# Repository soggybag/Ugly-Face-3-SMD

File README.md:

# Ugly Face 3 (SMD)

*Silkscreen name: Deformis v2.*

A gated, envelope-controlled square-wave synth fuzz for guitar, in a Hammond 1590B. A TL072 preamp (gain 201) gates and bends a TLC555 oscillator, with a **MIX** control to blend the dry fuzz with the synth tone. SMD parts are assembled by JLCPCB; the pots, LED, vactrol and wiring are hand-soldered.

## How it works

The guitar is amplified ×201 by U1A into a clipped square, which then does three things:

1. **Gate.** It's AC-coupled onto the 555's RESET pin. THRESHOLD sets the bias around the 555's ~1.0 V reset point, so the oscillator switches on and off every guitar cycle and restarts in step with the note (hard sync).
2. **Pitch bend.** It lights a DIY vactrol (LED + LDR). The LDR sits across the 555's timing resistance, so playing harder raises the pitch.
3. **Dry path.** It feeds the MIX control. U1B sums the dry fuzz and the 555 square (×4.1) → VOLUME → OUT.

Schematic: [UglyFace_03_schematic.pdf](UglyFace_03_schematic.pdf) · Layout: [UglyFace_03_layout.pdf](UglyFace_03_layout.pdf)

## Controls

| Knob | Part | Function |
|---|---|---|
| ENVELOPE | RV1 A10k (v1.3; v1.1 B1k) | How much the playing level drives the vactrol (pitch bend); fully CCW = off |
| THRESHOLD | SW1 toggle (v1.1) | GATED / GLITCH / ON. GLITCH sits on the 555's reset threshold, set once with the RV2 trimmer |
| FREQUENCY | RV3 C100k | Oscillator pitch (measured ~33 Hz to ~5 kHz) |
| MIX | RV4 B10k | Clean guitar (v1.1) ↔ synth square |
| VOLUME | RV5 A100k | Output level |

## Build notes

- **Hand-soldered:** four Alpha 16 mm pots, the THRESHOLD toggle (Taiway 100 ON-OFF-ON), the RV2 3362P 10k trimmer, the 3 mm LED (D2), the DIY vactrol U3 (LED + LDR in heat-shrink or a light-tight box), and the wire pads (9V/GND, IN/IG, OUT/OG, LED−/LG).
- **v1.0 boards only, recommended mod:** tack a **100 µF electrolytic across C4** (+ to VB, the MIX pot's middle-pin side). The stock 22 µF ceramic loses capacitance at 4.4 V. Without the mod, oscillator ripple on VB feeds back through the gain-201 preamp into the gate, and THRESHOLD becomes very sticky (on at 75%, off at 25%).
- Power: 9 V centre-negative; SS14 series reverse-polarity protection; ~4.3 mA (+ ~3.5 mA LED).

## Status

- **v1.1 (2026-10-03, JLC files generated):** C4 100 µF, 22k into RESET, RC-filtered 555 supply, C7 2.2 µ, C12/C13 1 µ, clean dry path (U4A) for MIX, buffered VB (U4B), THRESHOLD toggle + GLITCH trimmer. Details in [docs/Build Notes.md](docs/Build%20Notes.md).
- **v1.3 (2026-10-19, JLC files generated, not ordered):** new envelope (U5 LM358 detector from the clean DRY_OUT, Q1 current sink for the vactrol LED, DECAY trimmer RV6), ENVELOPE pot A10k, BAT54S RESET clamp, R21 15k, R13 220k, slotted Taiway footprint. Details: [docs/v1.3 Envelope.md](docs/v1.3%20Envelope.md).

- Boards received from JLCPCB 2026-10-01; bench tested 2026-10-02; **working with a guitar.** Measurements: [docs/Test Procedure.md](docs/Test%20Procedure.md).
- **Known issues (v1.0) / next revision** ([docs/Build Notes.md](docs/Build%20Notes.md)):
  - C4 → 100 µF.
  - FREQUENCY low end too low (33 Hz); C10 470n ceramic behaves like ~235n under bias, so use a film/C0G cap and retune.
  - Envelope weak (LDR choice / LED drive).
  - C12/C13 coupling caps cut below ~100 Hz.
  - Series resistor on the 555 RESET pin (CMOS protection; the pin is driven below ground every cycle).
  - THRESHOLD could become a 3-position switch.
- Ideas for the family: [Ugly Face Roadmap.md](Ugly%20Face%20Roadmap.md).

## Repository layout

```
UglyFace_03.kicad_pro / .kicad_sch / .kicad_pcb / .kicad_dru   KiCad 10 project
UglyFace.pretty/, fp-lib-table                              project footprints
3dmodels/        pot and enclosure models (${KIPRJMOD})
docs/            test procedure (with measurements) and build notes
enclosure/       panel art (Affinity + PDF/SVG exports)
*.pdf, *.png     schematic, layout and renders
```

Opens with KiCad 10. Libraries and 3D models are project-local or from KiCad's standard library.

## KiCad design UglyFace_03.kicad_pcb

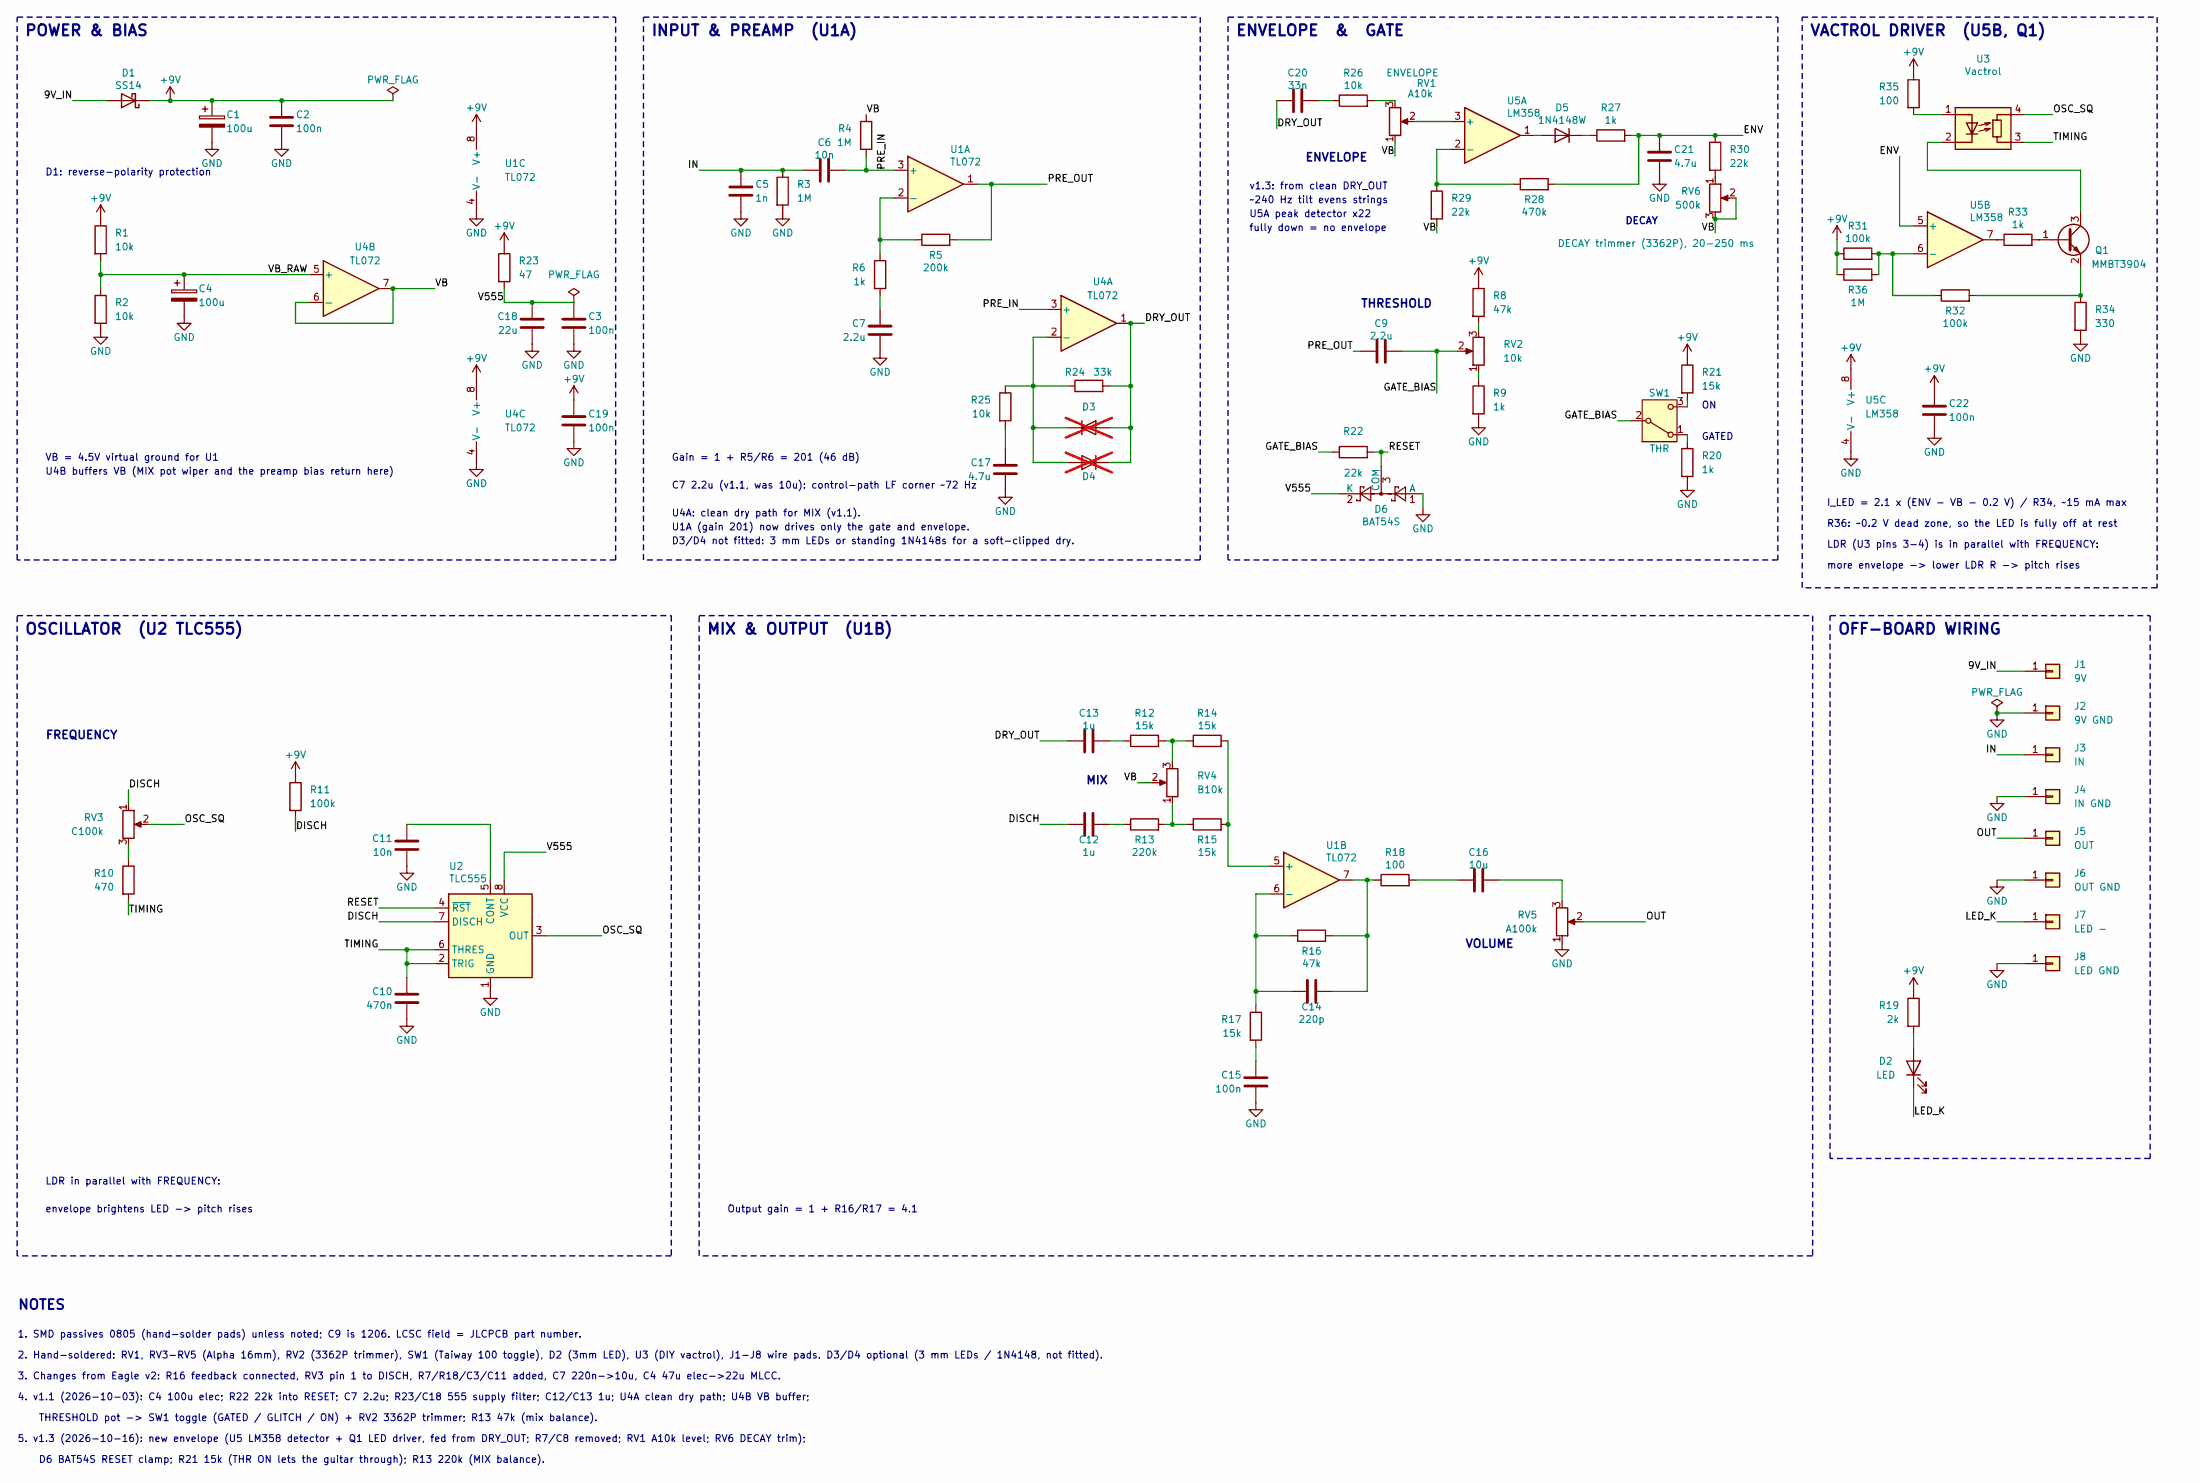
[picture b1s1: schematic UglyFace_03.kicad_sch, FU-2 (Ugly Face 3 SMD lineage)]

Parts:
C1, C4: 100u; CP_Elec_6.3x7.7; LCSC C970685
C2, C3, C15, C19, C22: 100n; C_0805_2012Metric_Pad1.18x1.45mm_HandSolder; LCSC C49678
C5: 1n; C_0805_2012Metric_Pad1.18x1.45mm_HandSolder; LCSC C46653
C6, C11: 10n; C_0805_2012Metric_Pad1.18x1.45mm_HandSolder; LCSC C1710
C7: 2.2u; C_0805_2012Metric_Pad1.18x1.45mm_HandSolder; LCSC C377773
C9: 2.2u; C_1206_3216Metric_Pad1.33x1.80mm_HandSolder; LCSC C50254
C10: 470n; C_0805_2012Metric_Pad1.18x1.45mm_HandSolder; LCSC C13967
C12, C13: 1u; C_0805_2012Metric_Pad1.18x1.45mm_HandSolder; LCSC C28323
C14: 220p; C_0805_2012Metric_Pad1.18x1.45mm_HandSolder; LCSC C107145
C16: 10u; C_0805_2012Metric_Pad1.18x1.45mm_HandSolder; LCSC C15850
C17, C21: 4.7u; C_0805_2012Metric_Pad1.18x1.45mm_HandSolder; LCSC C1779
C18: 22u; C_1206_3216Metric_Pad1.33x1.80mm_HandSolder; LCSC C12891
C20: 33n; C_0805_2012Metric_Pad1.18x1.45mm_HandSolder; LCSC C1739
D1: SS14; D_SMA_Handsoldering; LCSC C2480
D2: LED; LED_D3.0mm
D3, D4: 1N4148/LED; D_THT_Standing_3mm_P2.54_Compact; not fitted
D5: 1N4148W; D_SOD-123; LCSC C81598
D6: BAT54S; SOT-23; LCSC C19726
J1: 9V; SolderWire-0.5sqmm_1x01_D0.9mm_OD2.1mm
J2: 9V GND; SolderWire-0.5sqmm_1x01_D0.9mm_OD2.1mm
J3: IN; SolderWire-0.5sqmm_1x01_D0.9mm_OD2.1mm
J4: IN GND; SolderWire-0.5sqmm_1x01_D0.9mm_OD2.1mm
J5: OUT; SolderWire-0.5sqmm_1x01_D0.9mm_OD2.1mm
J6: OUT GND; SolderWire-0.5sqmm_1x01_D0.9mm_OD2.1mm
J7: LED -; SolderWire-0.5sqmm_1x01_D0.9mm_OD2.1mm
J8: LED GND; SolderWire-0.5sqmm_1x01_D0.9mm_OD2.1mm
Q1: MMBT3904; SOT-23; LCSC C20526
R1, R2, R25, R26: 10k; R_0805_2012Metric_Pad1.20x1.40mm_HandSolder; LCSC C17414
R3, R4, R36: 1M; R_0805_2012Metric_Pad1.20x1.40mm_HandSolder; LCSC C17514
R5: 200k; R_0805_2012Metric_Pad1.20x1.40mm_HandSolder; LCSC C17539
R6, R9, R20, R27, R33: 1k; R_0805_2012Metric_Pad1.20x1.40mm_HandSolder; LCSC C17513
R8, R16: 47k; R_0805_2012Metric_Pad1.20x1.40mm_HandSolder; LCSC C17713
R10: 470; R_0805_2012Metric_Pad1.20x1.40mm_HandSolder; LCSC C17710
R11, R31, R32: 100k; R_0805_2012Metric_Pad1.20x1.40mm_HandSolder; LCSC C149504
R12, R14, R15, R17, R21: 15k; R_0805_2012Metric_Pad1.20x1.40mm_HandSolder; LCSC C17475
R13: 220k; R_0805_2012Metric_Pad1.20x1.40mm_HandSolder; LCSC C17556
R18, R35: 100; R_0805_2012Metric_Pad1.20x1.40mm_HandSolder; LCSC C17408
R19: 2k; R_0805_2012Metric_Pad1.20x1.40mm_HandSolder; LCSC C17604
R22, R29, R30: 22k; R_0805_2012Metric_Pad1.20x1.40mm_HandSolder; LCSC C17560
R23: 47; R_0805_2012Metric_Pad1.20x1.40mm_HandSolder; LCSC C17714
R24: 33k; R_0805_2012Metric_Pad1.20x1.40mm_HandSolder; LCSC C17633
R28: 470k; R_0805_2012Metric_Pad1.20x1.40mm_HandSolder; LCSC C17709
R34: 330; R_0805_2012Metric_Pad1.20x1.40mm_HandSolder; LCSC C17630
RV1: A10k; Potentiometer_Alpha_16mm_Vertical
RV2: 10k; Potentiometer_Bourns_3362P_Vertical
RV3: C100k; Potentiometer_Alpha_16mm_Vertical
RV4: B10k; Potentiometer_Alpha_16mm_Vertical
RV5: A100k; Potentiometer_Alpha_16mm_Vertical
RV6: 500k; Potentiometer_Bourns_3362P_Vertical
SW1: THR; SW_Taiway_100_SPDT_PC
U1, U4: TL072; SOIC-8_3.9x4.9mm_P1.27mm; LCSC C6961
U2: TLC555; SOIC-8_3.9x4.9mm_P1.27mm; LCSC C6987
U3: Vactrol; Vactrol_LED_LDR_DIY
U5: LM358; SOIC-8_3.9x4.9mm_P1.27mm; LCSC C7950

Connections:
/9V_IN: D1.2 (A), J1.1
/DISCH: C12.1, R11.2, RV3.1, U2.7 (DISCH)
/DRY_OUT: C13.1, C20.1, D3.2 (A), D4.1 (K), R24.2, U4.1
/ENV: C21.1, R27.2, R28.2, R30.1, U5.5 (+)
/GATE_BIAS: C9.2, R22.1, RV2.2, SW1.2 (B)
/IN: C5.1, C6.1, J3.1, R3.1
/LED_K: D2.1 (K), J7.1
/OSC_SQ: RV3.2, U2.3 (OUT), U3.4 (R)
/OUT: J5.1, RV5.2
/PRE_IN: C6.2, R4.2, U1.3 (+), U4.3 (+)
/PRE_OUT: C9.1, R5.2, U1.1
/RESET: D6.3 (COM), R22.2, U2.4 (~RST)
/TIMING: C10.1, R10.2, U2.2 (TRIG), U2.6 (THRES), U3.3 (R)
/V555: C3.1, C18.1, D6.2 (K), R23.2, U2.8 (VCC)
/VB: R4.1, R29.2, RV1.1, RV4.2, RV6.2, RV6.3, U4.6 (-), U4.7
/VB_RAW: C4.1, R1.2, R2.1, U4.5 (+)
unnamed: C7.1, R6.2
unnamed: C12.2, R13.1
unnamed: C13.2, R12.1
unnamed: C14.2, R16.2, R18.1, U1.7
unnamed: C15.1, R17.2
unnamed: C16.1, R18.2
unnamed: C16.2, RV5.3
unnamed: C17.1, R25.2
unnamed: C20.2, R26.1
unnamed: D2.2 (A), R19.2
unnamed: D3.1 (K), D4.2 (A), R24.1, R25.1, U4.2 (-)
unnamed: D5.2 (A), U5.1
unnamed: D5.1 (K), R27.1
unnamed: Q1.1 (B), R33.2
unnamed: Q1.3 (C), U3.2 (K)
unnamed: Q1.2 (E), R32.2, R34.1
unnamed: R8.2, RV2.3
unnamed: R9.1, RV2.1
unnamed: R10.1, RV3.3
unnamed: R12.2, R14.1, RV4.3
unnamed: R13.2, R15.1, RV4.1
unnamed: R26.2, RV1.3
unnamed: R30.2, RV6.1
unnamed: R33.1, U5.7
unnamed: R20.1, SW1.1 (A)
unnamed: R21.2, SW1.3 (C)
unnamed: R5.1, R6.1, U1.2 (-)
unnamed: R14.2, R15.2, U1.5 (+)
unnamed: C14.1, R16.1, R17.1, U1.6 (-)
unnamed: C11.1, U2.5 (CONT)
unnamed: R35.2, U3.1 (A)
unnamed: RV1.2, U5.3 (+)
unnamed: R28.1, R29.1, U5.2 (-)
unnamed: R31.2, R32.1, R36.2, U5.6 (-)

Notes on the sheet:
envelope brightens LED -> pitch rises
U1A (gain 201) now drives only the gate and envelope.
POWER & BIAS
LDR (U3 pins 3-4) is in parallel with FREQUENCY:
THRESHOLD pot -> SW1 toggle (GATED / GLITCH / ON) + RV2 3362P trimmer; R13 47k (mix balance).
D6 BAT54S RESET clamp; R21 15k (THR ON lets the guitar through); R13 220k (MIX balance).
INPUT & PREAMP (U1A)
VACTROL DRIVER (U5B, Q1)
4. v1.1 (2026-10-03): C4 100u elec; R22 22k into RESET; C7 2.2u; R23/C18 555 supply filter; C12/C13 1u; U4A clean dry path; U4B VB buffer;
1. SMD passives 0805 (hand-solder pads) unless noted; C9 is 1206. LCSC field = JLCPCB part number.
2. Hand-soldered: RV1, RV3-RV5 (Alpha 16mm), RV2 (3362P trimmer), SW1 (Taiway 100 toggle), D2 (3mm LED), U3 (DIY vactrol), J1-J8 wire pads. D3/D4 optional (3 mm LEDs / 1N4148, not fitted).
R36: ~0.2 V dead zone, so the LED is fully off at rest
Gain = 1 + R5/R6 = 201 (46 dB)
GATED
VB = 4.5V virtual ground for U1
VOLUME
v1.3: from clean DRY_OUT
THRESHOLD
U5A peak detector x22
5. v1.3 (2026-10-16): new envelope (U5 LM358 detector + Q1 LED driver, fed from DRY_OUT; R7/C8 removed; RV1 A10k level; RV6 DECAY trim);
more envelope -> lower LDR R -> pitch rises
D1: reverse-polarity protection
DECAY
U4A: clean dry path for MIX (v1.1).
NOTES
~240 Hz tilt evens strings
OFF-BOARD WIRING
OSCILLATOR (U2 TLC555)
I_LED = 2.1 x (ENV - VB - 0.2 V) / R34, ~15 mA max
ENVELOPE
C7 2.2u (v1.1, was 10u): control-path LF corner ~72 Hz
ENVELOPE & GATE
FREQUENCY
MIX & OUTPUT (U1B)
D3/D4 not fitted: 3 mm LEDs or standing 1N4148s for a soft-clipped dry.
fully down = no envelope
LDR in parallel with FREQUENCY:
Output gain = 1 + R16/R17 = 4.1
U4B buffers VB (MIX pot wiper and the preamp bias return here)
MIX

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
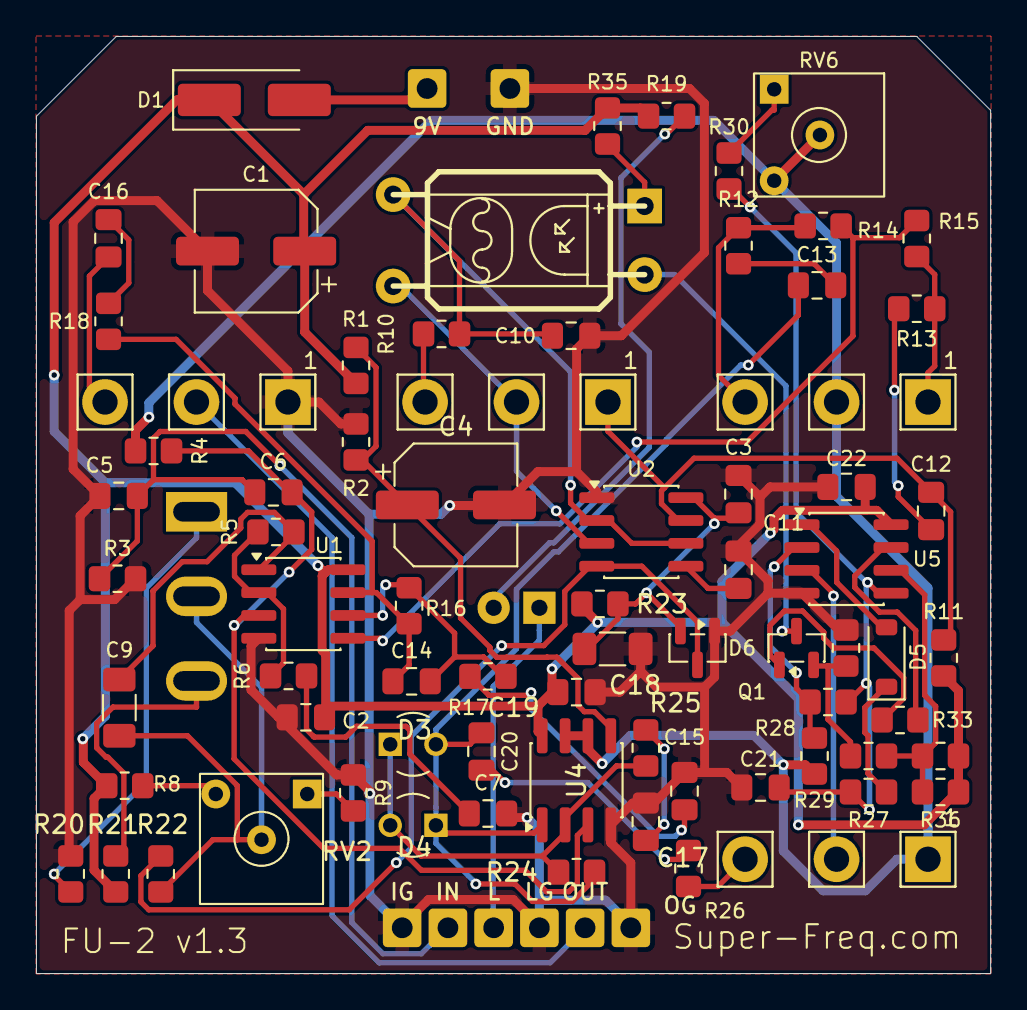
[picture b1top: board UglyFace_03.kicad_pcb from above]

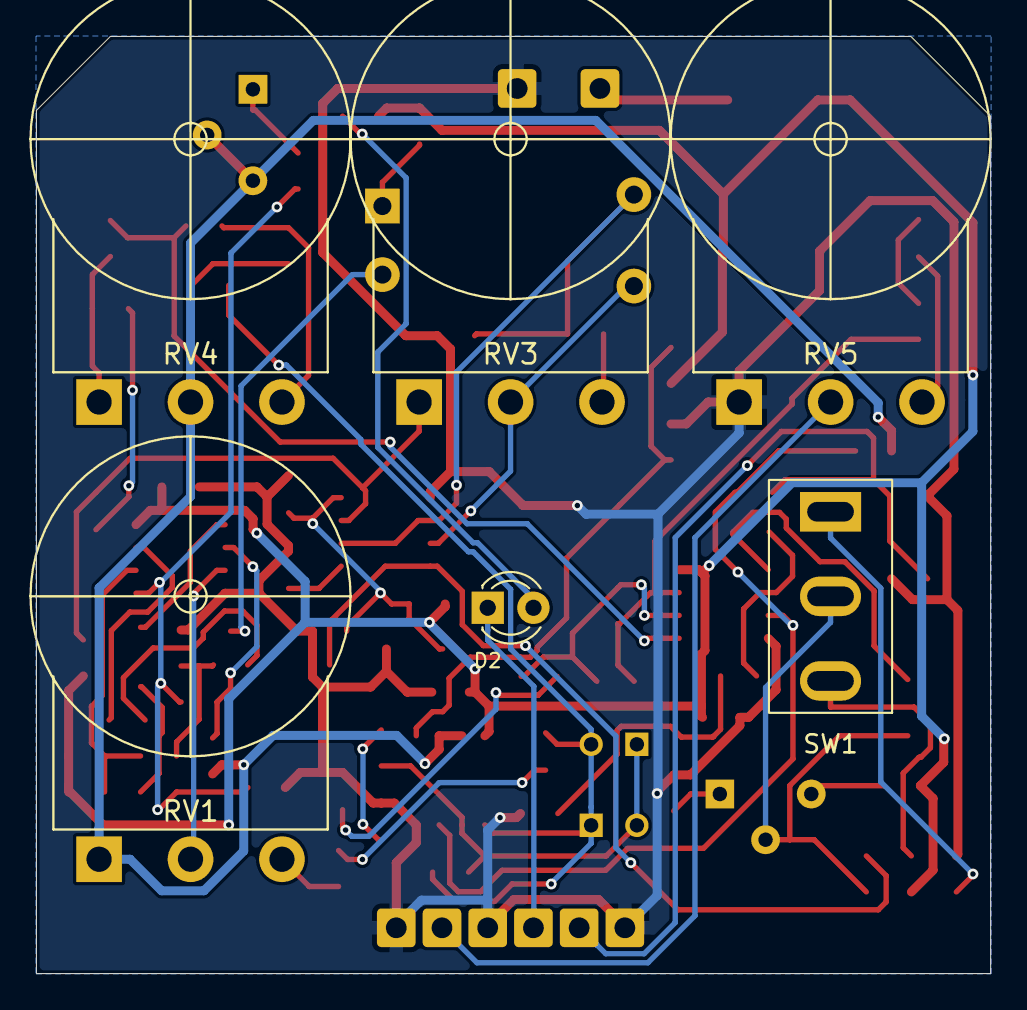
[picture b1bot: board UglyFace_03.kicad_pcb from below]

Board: 2 copper layers, 53.0 x 52.1 mm, 84 parts (3 on the bottom side), 52 nets.

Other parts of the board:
ENC1: Hammond 1590B; Hammond_1590B
